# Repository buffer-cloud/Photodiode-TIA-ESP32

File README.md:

# Photodiode TIA + ESP32 Optical Sensor

Photodiode transimpedance amplifier with ESP32 wireless acquisition and Python-based signal analysis and a live Flutter dashboard. The analog noise budget is quantified in µV (CALCULATED); end-to-end resolution is expected to be limited by the ESP32 ADC, so no system-level "low-noise" claim is made until measured.

**Status:** Revision A analog design and simulation gate PASS; schematic, PCB, firmware and Python tools complete. The BOM and fabrication exports are complete for bare-board prototype fabrication. Component qualification and physical validation remain pending. BPW34 remains the provisional detector. All physical results are **TBD — HARDWARE MEASUREMENT REQUIRED**. See [implementation verification](docs/implementation-verification.md), [manufacturing notes](hardware/manufacturing/rev-a/fabrication-notes.md) and the [bring-up plan](docs/bringup-plan.md).

## Repository structure

- `docs/`: requirements, architecture, calculations and verification
- `simulation/`: LTspice circuits and reproducible analysis
- `hardware/`: KiCad design, BOM and manufacturing notes
- `firmware/esp32/`: acquisition and WebSocket telemetry
- `software/python/`: dashboard and analysis
- `software/flutter/`: responsive live ESP32 dashboard for Chrome
- `measurements/`: real bench data only
- `portfolio/`: case study and factual résumé entry

## ESP32 live dashboard

The standalone ESP32 Dev Module has been built, uploaded, and verified over Wi-Fi/WebSocket. Open the [Flutter dashboard guide](software/flutter/README.md) for Chrome and Android setup. The interface displays live raw ADC counts and packet health, with an explicit warning that GPIO34 is currently unconnected. Physical photodiode performance remains unverified until the PCB is assembled.

## Phase-sensitive sensing research

The [research track](research/phase-sensitive/README.md) adds a reproducible synthetic lock-in comparison and a preliminary physical ESP32 stream-health measurement. It defines the electrical and optical experiments needed to turn the current prototype into a characterized instrument. The synthetic results are not optical measurements, and the first stream check exposed a delivery-rate issue requiring controlled follow-up.

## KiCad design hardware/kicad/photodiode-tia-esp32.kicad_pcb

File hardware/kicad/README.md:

# Photodiode TIA / ESP32 — native KiCad 9

Open `photodiode-tia-esp32.kicad_pro`. The native schematic is the editable source of truth. It uses one A3 sheet with supply, reference, bypass, detector/TIA, paired gain branches, buffered filter/ADC and test-point sections. `Photodiode.kicad_sym` and both library tables are project-relative; install standard KiCad 9 footprint libraries.

`verification/pin-review.md` records manufacturer pin checks and executed ERC/export checks. Generated `verification/schematic.xml`, `schematic.pdf`, and `erc.rpt` are local review outputs and can be regenerated with KiCad CLI.

`build_schematic.py` preserves the initial capture recipe, not an automatic synchronization mechanism. It refuses to replace an existing schematic unless `--overwrite` is explicitly passed. **That flag discards manual schematic/library edits.** Make a backup or use a separate checkout first. Symbol-library discovery supports `--symbol-library PATH`, `KICAD_SYMBOL_DIR`, then conventional Linux/macOS/Windows KiCad 9 installation paths. The checked-in native schematic does not require Python or this recipe to open/edit.

The custom Vishay BPW34 footprint defines pin1=cathode, pin2=anode, 5.1 mm pitch; see the pin-review evidence. No PCB is created by this capture recipe.

Operate with exactly one gain shunt. Power off before changing it. Open JP_ADC for independent powering; clamps are not powered-off isolation. Prototype checks and rail-ramp verification are required before connecting the ADC link.

## Routed PCB

The native PCB is fully routed on two layers, 60 × 45 mm, 1.6 mm thick. Executed all-severity DRC with schematic parity passes with zero violations, zero unconnected items and zero parity issues; see `verification/drc.rpt` and `verification/layout-review.md`. `verification/board-top.png` is the reviewed top rendering. `verification/assembly-top.svg` supplies visible numeric component references. Vias are off SMD pads; manufacturing-output review and bench-validation limits are documented in the layout review.

Use the saved PCB as the authoritative design. `repair_pcb.py --output NEW_PATH` creates a separate candidate without overwriting any existing file. The native project does not run this script on opening. The defective initial routing recipe and intermediate candidates are retained only in ignored local recovery storage.

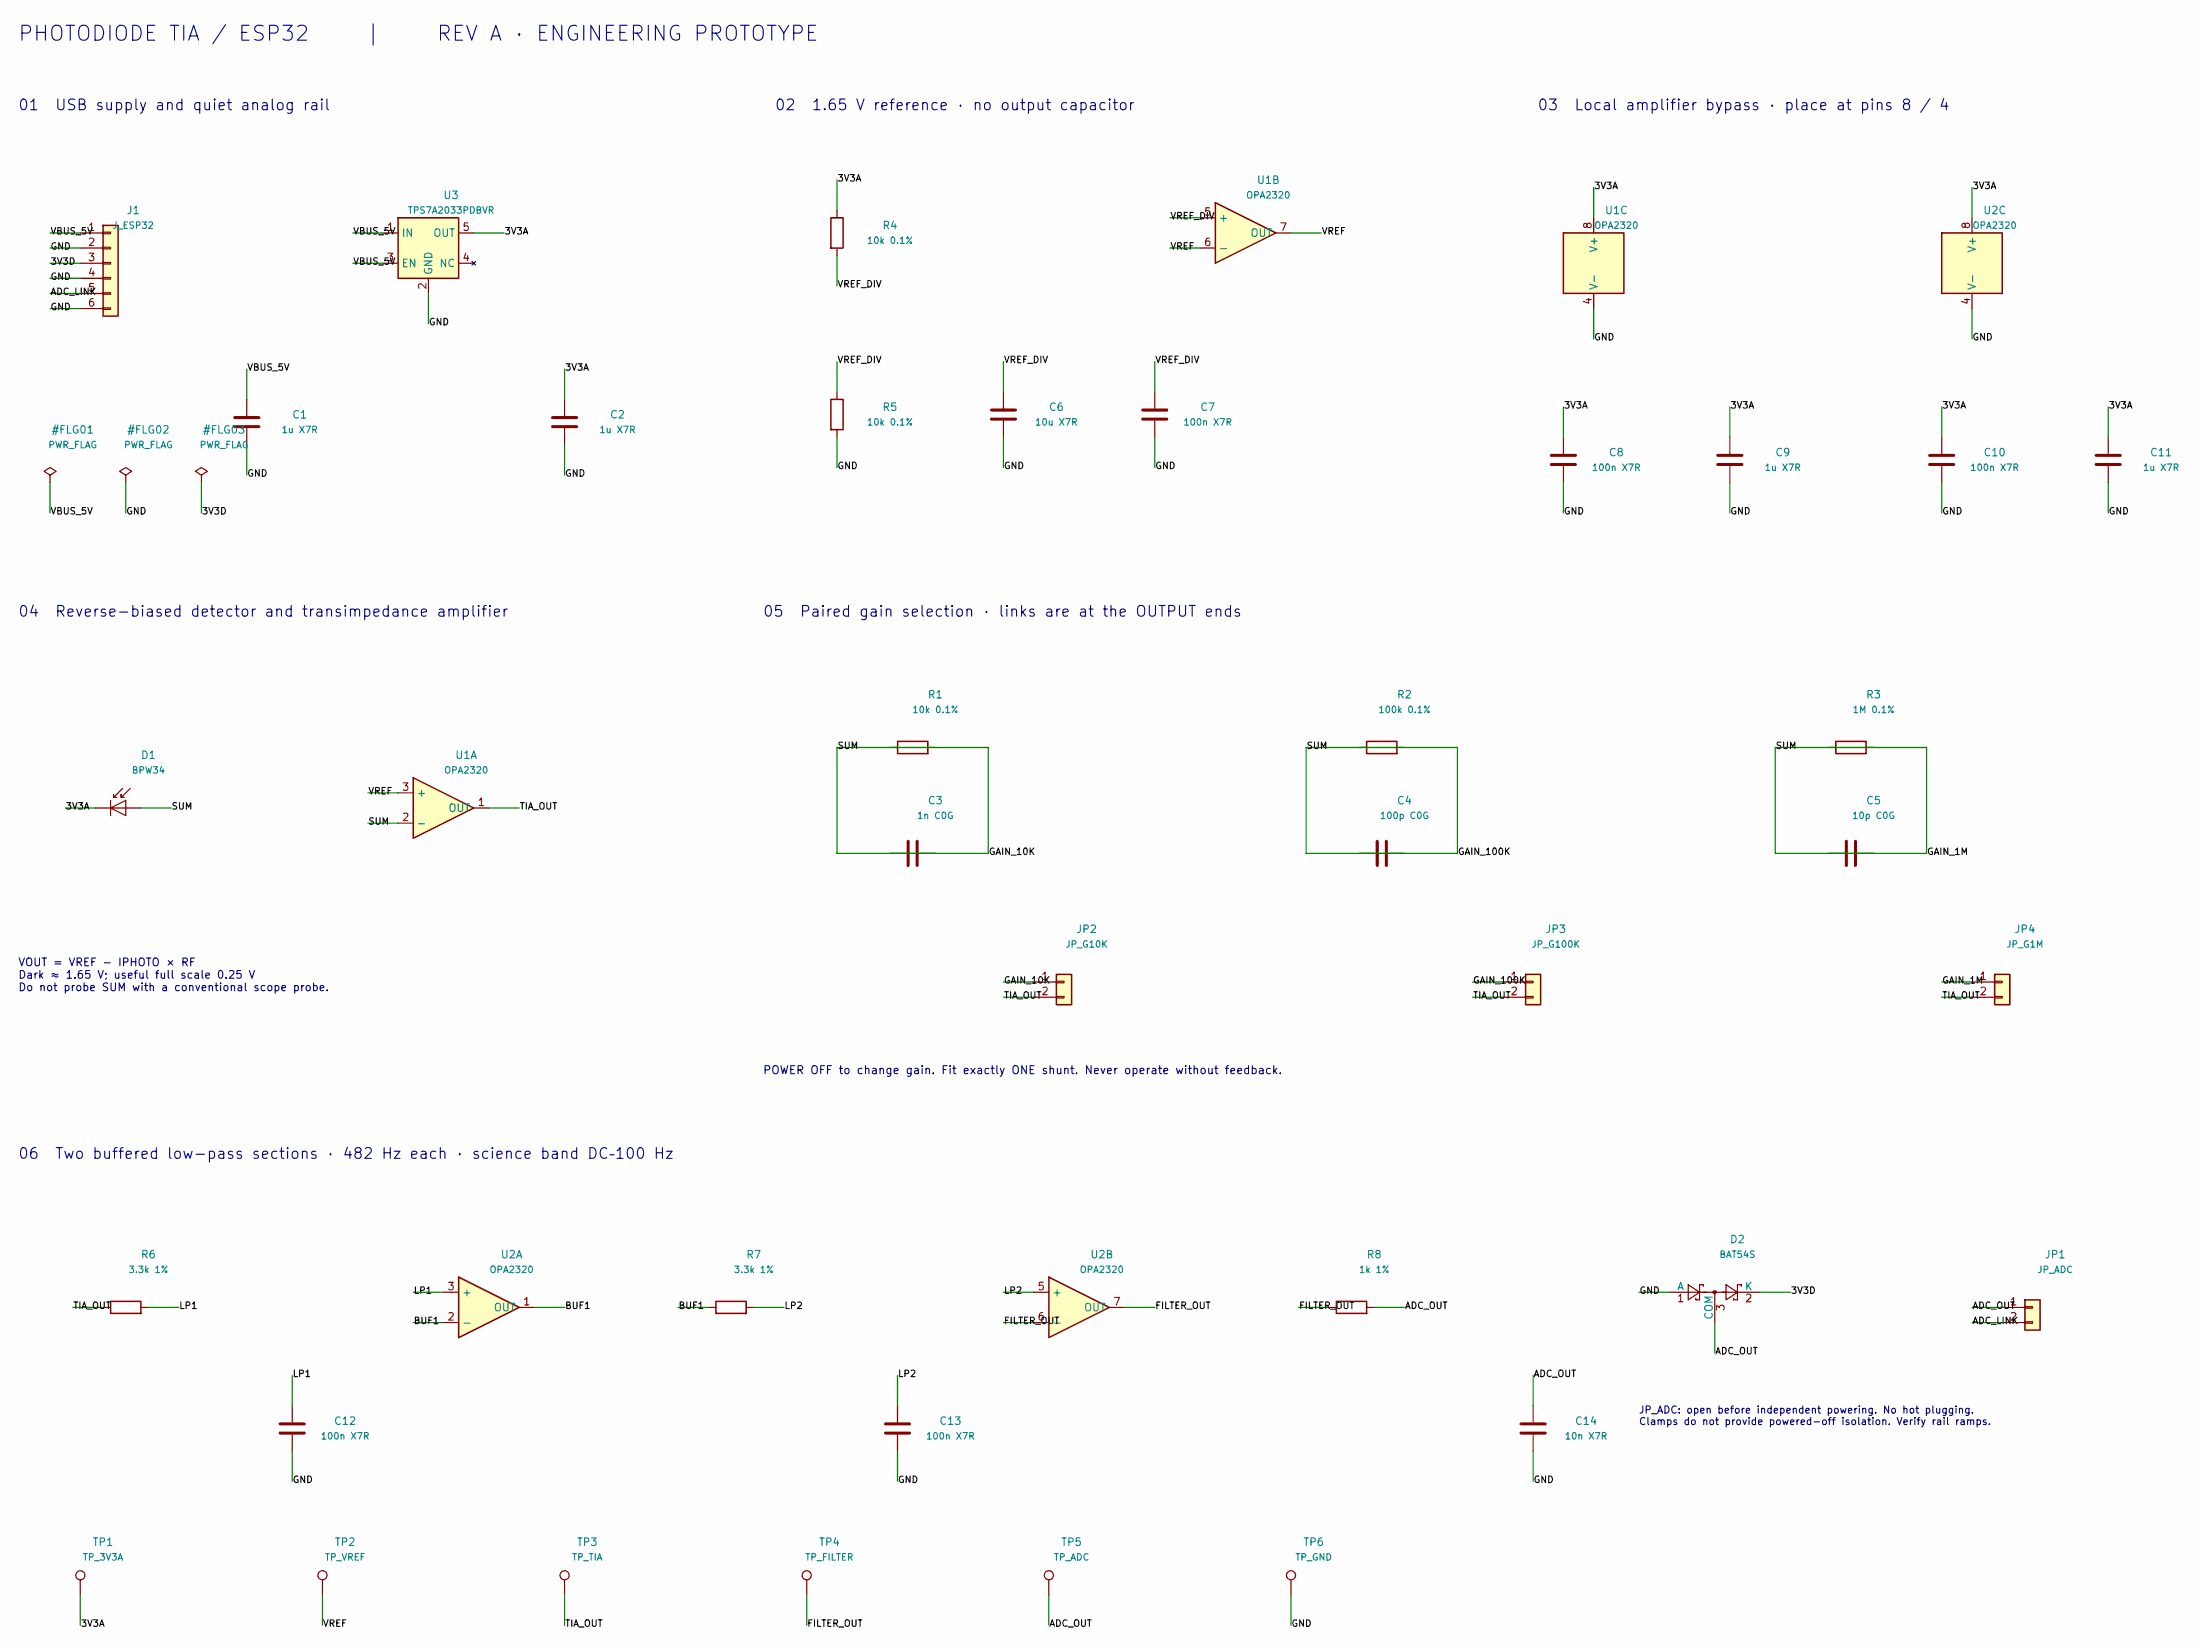
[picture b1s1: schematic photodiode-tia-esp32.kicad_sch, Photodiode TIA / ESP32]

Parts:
C1, C2, C9, C11: 1u X7R; C_0603_1608Metric
C3: 1n C0G; C_0603_1608Metric
C4: 100p C0G; C_0603_1608Metric
C5: 10p C0G; C_0603_1608Metric
C6: 10u X7R; C_0603_1608Metric
C7, C8, C10, C12, C13: 100n X7R; C_0603_1608Metric
C14: 10n X7R; C_0603_1608Metric
D1: BPW34; Vishay_BPW34_THT
D2: BAT54S; SOT-23
J1: J_ESP32; PinHeader_1x06_P2.54mm_Vertical
JP1: JP_ADC; PinHeader_1x02_P2.54mm_Vertical
JP2: JP_G10K; PinHeader_1x02_P2.54mm_Vertical
JP3: JP_G100K; PinHeader_1x02_P2.54mm_Vertical
JP4: JP_G1M; PinHeader_1x02_P2.54mm_Vertical
R1, R4, R5: 10k 0.1%; R_0603_1608Metric
R2: 100k 0.1%; R_0603_1608Metric
R3: 1M 0.1%; R_0603_1608Metric
R6, R7: 3.3k 1%; R_0603_1608Metric
R8: 1k 1%; R_0603_1608Metric
TP1: TP_3V3A; TestPoint_Pad_D1.5mm
TP2: TP_VREF; TestPoint_Pad_D1.5mm
TP3: TP_TIA; TestPoint_Pad_D1.5mm
TP4: TP_FILTER; TestPoint_Pad_D1.5mm
TP5: TP_ADC; TestPoint_Pad_D1.5mm
TP6: TP_GND; TestPoint_Pad_D1.5mm
U1, U2: OPA2320; SOIC-8_3.9x4.9mm_P1.27mm
U3: TPS7A2033PDBVR; SOT-23-5

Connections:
/3V3A: C2.1, C8.1, C9.1, C10.1, C11.1, D1.1 (K), R4.1, TP1.1, U1.8 (V+), U2.8 (V+), U3.5 (OUT)
/3V3D: D2.2 (K), J1.3
/ADC_LINK: J1.5, JP1.2
/ADC_OUT: C14.1, D2.3 (COM), JP1.1, R8.2, TP5.1
/BUF1: R7.1, U2.1 (OUT), U2.2 (−)
/FILTER_OUT: R8.1, TP4.1, U2.6 (−), U2.7 (OUT)
/GAIN_1M: C5.1, JP4.1, R3.1
/GAIN_10K: C3.1, JP2.1, R1.1
/GAIN_100K: C4.1, JP3.1, R2.1
/GND: C1.2, C2.2, C6.2, C7.2, C8.2, C9.2, C10.2, C11.2, C12.2, C13.2, C14.2, D2.1 (A), J1.2, J1.4, J1.6, R5.2, TP6.1, U1.4 (V−), U2.4 (V−), U3.2 (GND)
/LP1: C12.1, R6.2, U2.3 (+)
/LP2: C13.1, R7.2, U2.5 (+)
/SUM: C3.2, C4.2, C5.2, D1.2 (A), R1.2, R2.2, R3.2, U1.2 (−)
/TIA_OUT: JP2.2, JP3.2, JP4.2, R6.1, TP3.1, U1.1 (OUT)
/VBUS_5V: C1.1, J1.1, U3.1 (IN), U3.3 (EN)
/VREF: TP2.1, U1.3 (+), U1.6 (−), U1.7 (OUT)
/VREF_DIV: C6.1, C7.1, R4.2, R5.1, U1.5 (+)

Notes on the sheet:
PHOTODIODE TIA / ESP32 | REV A · ENGINEERING PROTOTYPE
01 USB supply and quiet analog rail
02 1.65 V reference · no output capacitor
03 Local amplifier bypass · place at pins 8 / 4
04 Reverse-biased detector and transimpedance amplifier
VOUT = VREF − IPHOTO × RF Dark ≈ 1.65 V; useful full scale 0.25 V Do not probe SUM with a conventional scope probe.
05 Paired gain selection · links are at the OUTPUT ends
POWER OFF to change gain. Fit exactly ONE shunt. Never operate without feedback.
06 Two buffered low-pass sections · 482 Hz each · science band DC–100 Hz
JP_ADC: open before independent powering. No hot plugging. Clamps do not provide powered-off isolation. Verify rail ramps.

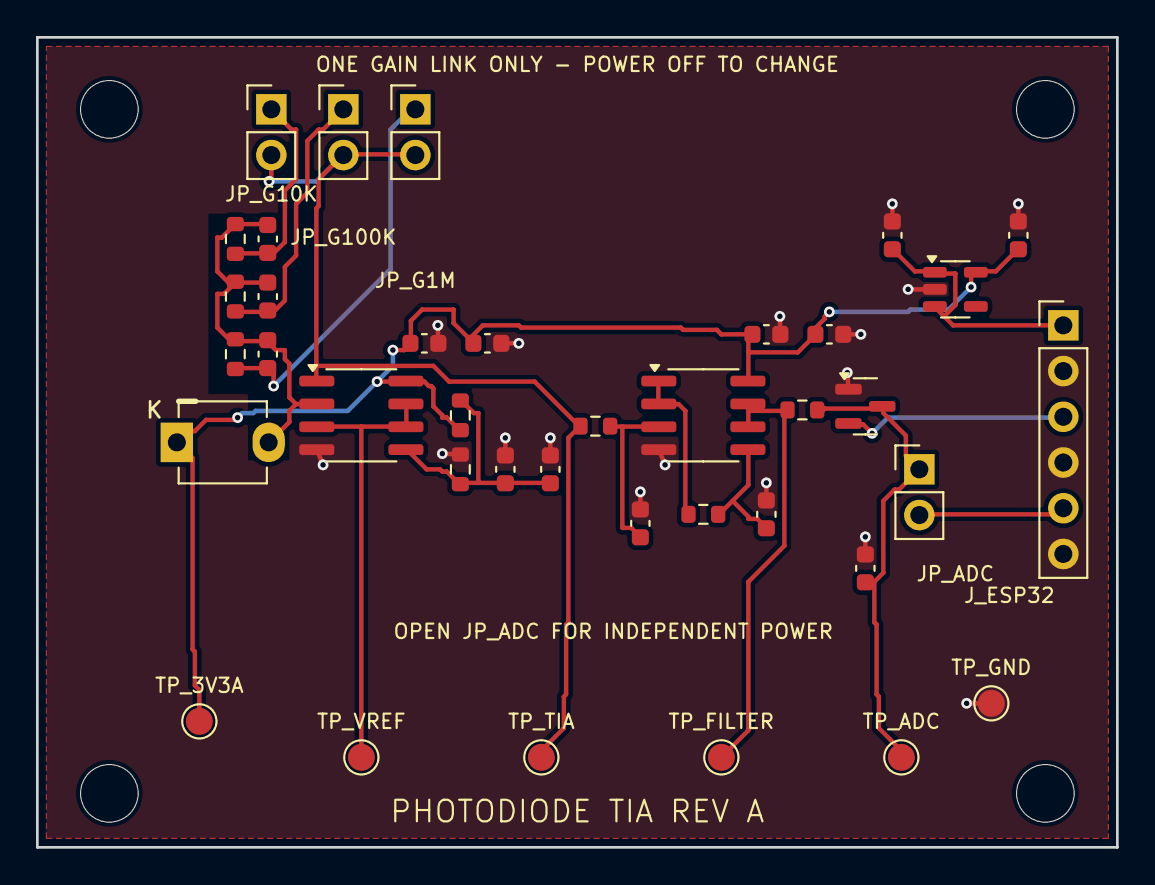
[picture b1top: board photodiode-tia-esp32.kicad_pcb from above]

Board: 2 copper layers, 60.0 x 45.0 mm, 42 parts (0 on the bottom side), 17 nets.

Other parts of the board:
MH1, MH2, MH3, MH4: M3; MountingHole_3.2mm_M3

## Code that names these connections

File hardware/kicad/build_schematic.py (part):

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def passive(kind,ref,val,x,y,n1,n2,angle=0):return add(kind,ref,val,x,y,{'1':n1,'2':n2},R if kind=='R' else C,angle=angle)
note('PHOTODIODE TIA / ESP32     |     REV A · ENGINEERING PROTOTYPE',20,15,2.5)
note('01  USB supply and quiet analog rail',20,27,1.8)
add('Conn_01x06','J1','J_ESP32',35.56,53.34,dict(zip(map(str,range(1,7)),['VBUS_5V','GND','3V3D','GND','ADC_LINK','GND'])),'Connector_PinHeader_2.54mm:PinHeader_1x06_P2.54mm_Vertical')
add('TPS7A2033PDBVR','U3','TPS7A2033PDBVR',88.9,50.8,{'1':'VBUS_5V','2':'GND','3':'VBUS_5V','4':None,'5':'3V3A'},'Package_TO_SOT_SMD:SOT-23-5')
passive('C','C1','1u X7R',58.42,80.01,'VBUS_5V','GND');passive('C','C2','1u X7R',111.76,80.01,'3V3A','GND')
for i,(net,x) in enumerate([('VBUS_5V',25.4),('GND',38.1),('3V3D',50.8)]):add('PWR_FLAG','#FLG0'+str(i+1),'PWR_FLAG',x,90.17,{'1':net})
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note('05  Paired gain selection · links are at the OUTPUT ends',145,112,1.8)
# Actual parallel branches, each isolated at output by link.
for i,(ref,val,cv,x) in enumerate([('10K','10k 0.1%','1n C0G',170.18),('100K','100k 0.1%','100p C0G',248.92),('1M','1M 0.1%','10p C0G',327.66)],1):
 p=add('R','R'+str(i),val,x,134.62,{'1':'SUM','2':'GAIN_'+ref},R,angle=90,autolabel=False)
 c=add('C','C'+str(i+2),cv,x,152.4,{'1':'SUM','2':'GAIN_'+ref},C,angle=90,autolabel=False)
 left=x-12.7;right=x+12.7
 for z in [p,c]:wire(z['1'],(right,z['1'][1]));wire(z['2'],(left,z['2'][1]))
 # Rotation 90: pin1 right, pin2 left. SUM at left would reverse passive nets only; label explicit.
 wire((left,134.62),(left,152.4));wire((right,134.62),(right,152.4));label('SUM',left,134.62);label('GAIN_'+ref,right,152.4)
 add('Conn_01x02','JP'+str(i+1),'JP_G'+ref,x+25.4,173.99,{'1':'GAIN_'+ref,'2':'TIA_OUT'},H)
note('POWER OFF to change gain. Fit exactly ONE shunt. Never operate without feedback.',145,189,1.35)
note('06  Two buffered low-pass sections · 482 Hz each · science band DC–100 Hz',20,203,1.8)
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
